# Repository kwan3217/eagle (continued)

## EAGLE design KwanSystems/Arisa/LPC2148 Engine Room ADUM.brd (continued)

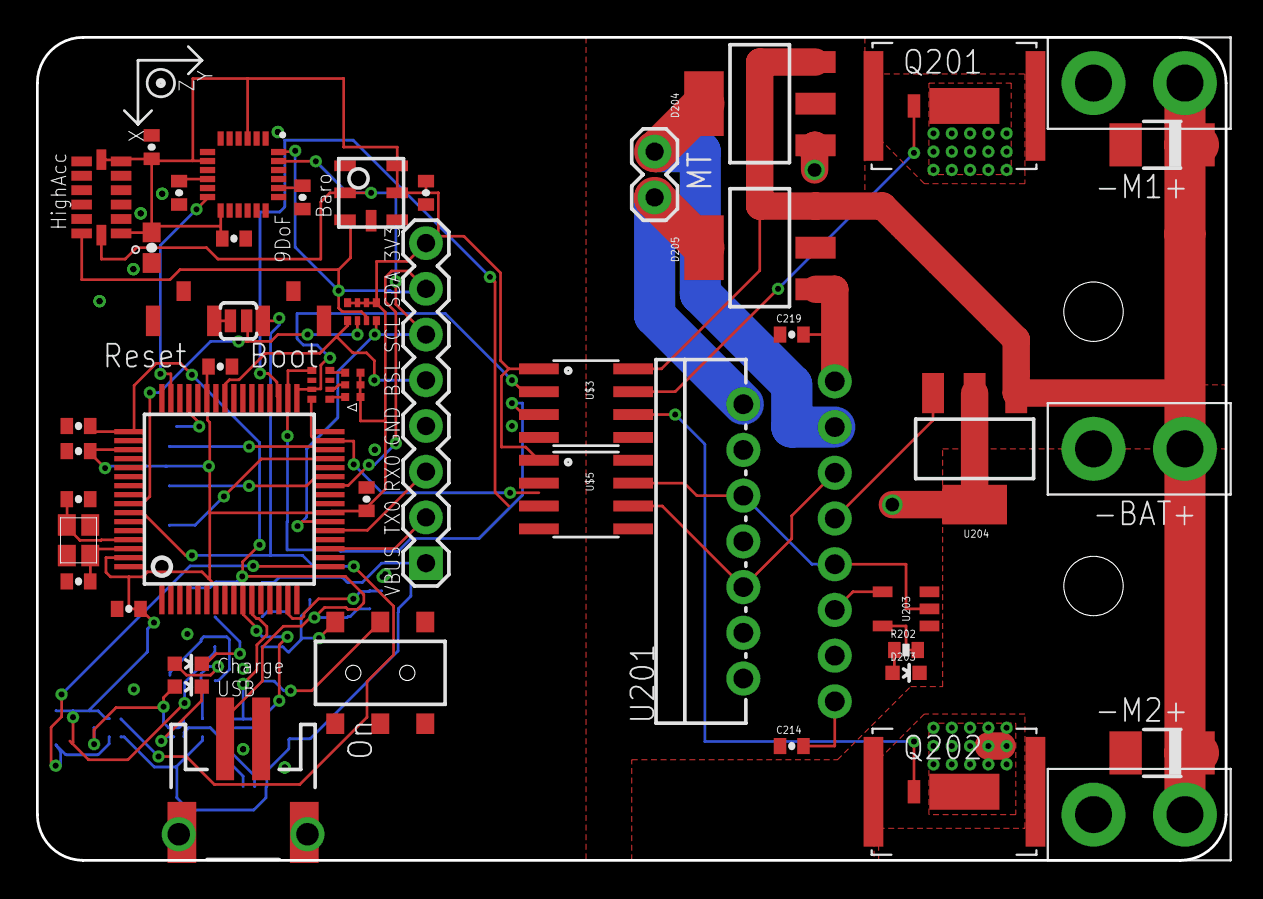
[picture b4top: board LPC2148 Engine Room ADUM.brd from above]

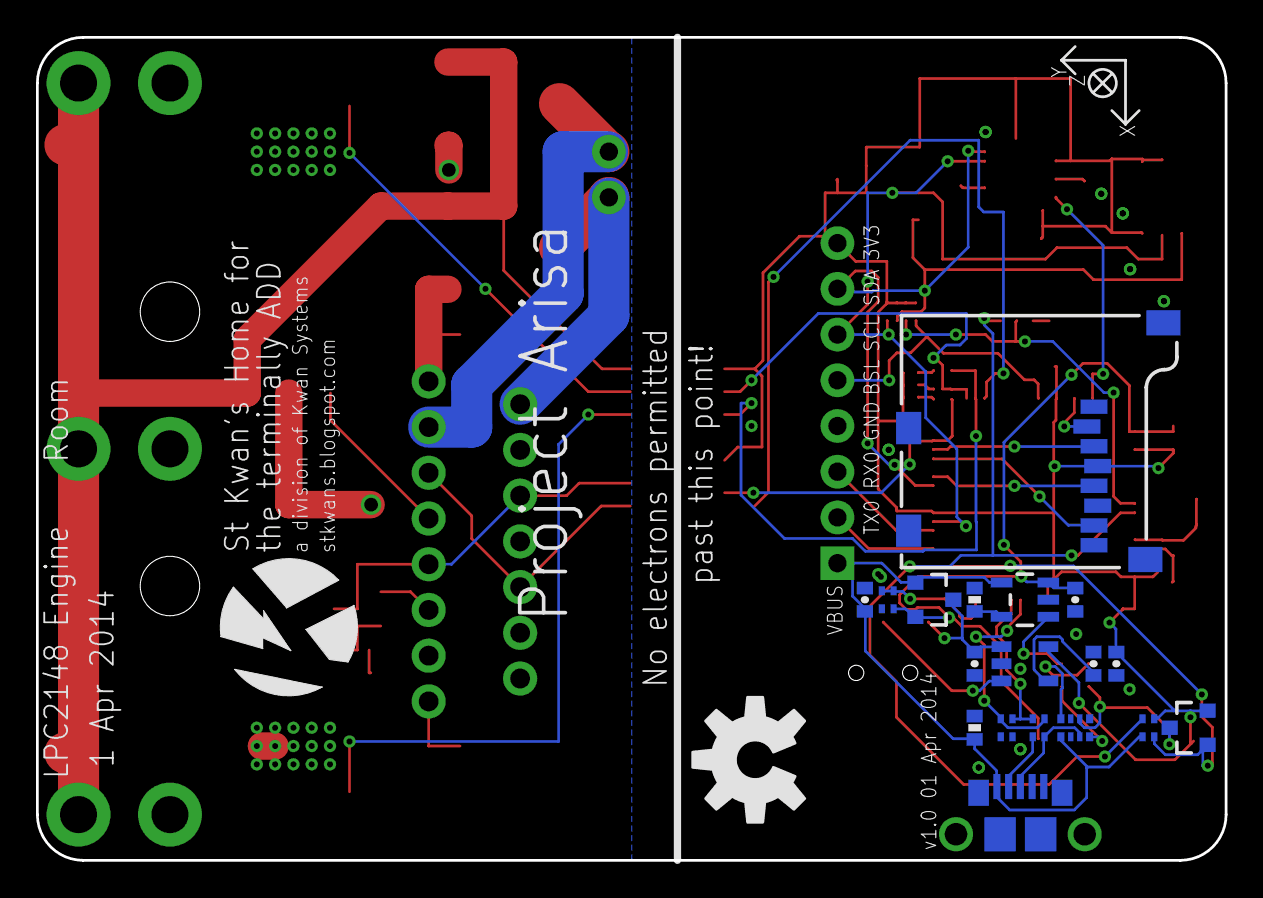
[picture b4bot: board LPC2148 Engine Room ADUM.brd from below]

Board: 2 copper layers, 66.0 x 45.7 mm, 71 parts (20 on the bottom side), 55 nets.

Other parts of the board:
U$1: KWAN_CIRCLE
U$2: OSHW-LOGO-L
U$4: AXES
